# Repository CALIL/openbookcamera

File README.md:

# Open Book Camera v1

汎用的なデバイスで構成される高速な書影撮影システム

## コンセプト

- 書影（本の表示画像）キャプチャ用のスキャナデバイス
- 本を置いたら自動撮影
- 表紙・裏表紙・背の3面を高速撮影（2秒程度）
- ネットワーク接続なしでスタンドアロン動作

## システム構成

## Installation

Windows:

- [Anaconda](https://www.anaconda.com/download/) Python3.7 をインストール
- [libjpeg-turbo](https://libjpeg-turbo.org/Documentation/Documentation) をインストール [libjpeg-turbo-1.5.3-vc64.exe](https://sourceforge.net/projects/libjpeg-turbo/files/1.5.3/libjpeg-turbo-1.5.3-vc64.exe/download)
- [Visual C++ Redistributable Packages for Visual Studio 2013](https://www.microsoft.com/en-US/download/details.aspx?id=40784)をインストール（pyzbarが依存）

```sh
conda install opencv==3.4.2
pip install -r requirements.txt
python capture.py
```

## キーボード操作

| キー | 役割                     |
|------|--------------------------|
| 0    | コントローラーリセット   |
| 1    | 上面のカメラに切り替える |
| 2    | 下面のカメラに切り替える |
| 3    | 背面のカメラに切り替える |
| 4    | 距離センサのテスト       |
| c    | カメラの設定画面を開く   |
| ESC  | システム終了             |
| Enter| 手動撮影                 |

1→c 2→c と操作することで各カメラの設定を順次調整できます。調整結果は保存されません。

## 制御ボード

- Arudinoシールド互換サイズ
- MOSFETによる12V制御回路×4
- 各種センサ向けのコネクタ（2.5mmピッチ・XHシリーズ）
- [Pololu Arduino library for VL53L0X](https://github.com/pololu/vl53l0x-arduino)
- 光電センサ [Z2T-2000N](https://www.optex-fa.jp/products/photo_sensor/amp/z_eco/index.html) を本が置かれたことを検出するセンサとして採用

## UVCカメラ

- [UVC規格](https://en.wikipedia.org/wiki/USB_video_device_class)の汎用的なUSBカメラに対応
- カーリルでは[IPEVO社製V4K](https://www.ipevo.jp/v4k.html)を採用（800万画素）
- 各カメラを独立したUSBポートに接続すること（USBハブを用いた場合は帯域不足となる）

## 注意事項

- 輸送後にはフォーカス設定が変動する場合があります。最適な画質になる設定にソースコードを調整してください。
- 2019年12月購入以降のV4Kにおいて、色温度の設定が自動化できない不具合を確認しています。この問題は[openCV側の不具合](https://github.com/opencv/opencv/issues/13130)の可能性があります。cコマンドによるマニュアル設定をお願いします。
 
## Release History

* 0.0.1 Work in progress
* 1.0.0 正式リリース
* 1.1.0 V4K最新ファームウェアに対応
* 1.2.0 V4K最新ファームウェアに対応

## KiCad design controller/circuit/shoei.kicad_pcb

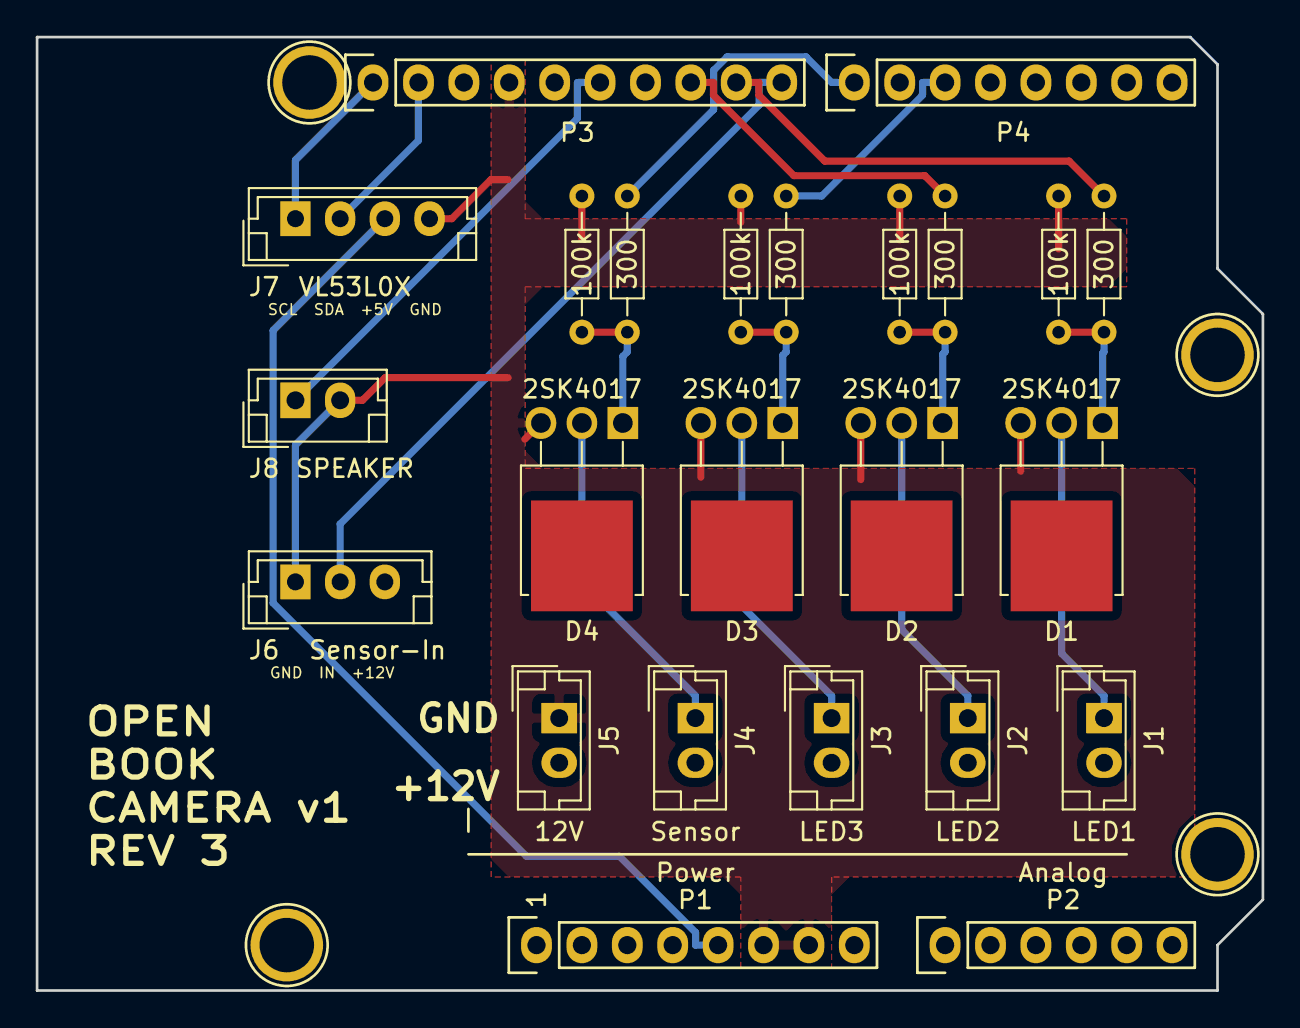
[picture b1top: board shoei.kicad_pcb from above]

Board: 2 copper layers, 68.6 x 53.3 mm, 28 parts (0 on the bottom side), 19 nets.

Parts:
D1, D2, D3, D4: 2SK4017; TO-251-3-1EP_Horizontal_TabDown
J1: LED1; JST_EH_B02B-EH-A_1x02_P2.50mm_Vertical
J2: LED2; JST_EH_B02B-EH-A_1x02_P2.50mm_Vertical
J3: LED3; JST_EH_B02B-EH-A_1x02_P2.50mm_Vertical
J4: Sensor; JST_EH_B02B-EH-A_1x02_P2.50mm_Vertical
J5: 12V; JST_EH_B02B-EH-A_1x02_P2.50mm_Vertical
J6: Sensor-In; JST_EH_B03B-EH-A_1x03_P2.50mm_Vertical
J7: VL53L0X; JST_EH_B04B-EH-A_1x04_P2.50mm_Vertical
J8: SPEAKER; JST_EH_B02B-EH-A_1x02_P2.50mm_Vertical
P1: Power; Socket_Strip_Arduino_1x08
P2: Analog; Socket_Strip_Arduino_1x06
P3: Digital; Socket_Strip_Arduino_1x10
P4: Digital; Socket_Strip_Arduino_1x08
P5, P6, P7, P8: CONN_01X01; Arduino_1pin
R1, R2, R3, R4: 300; R_Axial_DIN0204_L3.6mm_D1.6mm_P7.62mm_Horizontal
R5, R6, R7, R8: 100k; R_Axial_DIN0204_L3.6mm_D1.6mm_P7.62mm_Horizontal

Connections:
+5V: J7.3, P1.5
+12V: J1.2, J2.2, J3.2, J4.2, J5.2, J6.3, P1.8
/5(**): P4.3, R3.1
/7: P4.1, R4.1
/8: J6.2, P3.10
/9(**): P3.9, R1.1
/10(**/SS): P3.8, R2.1
/12(MISO): J8.1, P3.6
/A4(SDA): J7.2, P3.2
/A5(SCL): J7.1, P3.1
GND: D1.3, D2.3, D3.3, D4.3, J5.1, J6.1, J7.4, J8.2, P1.6, P1.7, P3.4, R5.2, R6.2, R7.2, R8.2
unnamed: D1.1, R1.2, R5.1
unnamed: D1.2, J1.1
unnamed: D2.1, R2.2, R6.1
unnamed: D2.2, J2.1
unnamed: D3.1, R3.2, R7.1
unnamed: D3.2, J3.1
unnamed: D4.1, R4.2, R8.1
unnamed: D4.2, J4.1

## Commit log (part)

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2018-08-17 add firmware/Controller.ino
2018-08-17 add circuit board (KiCad)
2018-08-17 add order data
2018-08-17 add 3d image
2018-08-17 add capture application
2018-08-18 use turbo-jpeg on save
2018-08-18 move capture.py
2018-08-18 add requirements.txt
2018-08-18 fix data-path
2018-08-18 document for installation
2018-08-18 add diagram.png
2018-08-18 add document
2018-08-18 add picture
2018-08-18 fix picture
2018-08-18 fix document
2018-08-18 update document
2018-08-18 add dependency to requirements.txt
2018-08-18 fix doc
2018-08-18 add doc
2018-08-18 change serial rate to 115200
2018-08-18 fix lunch check process
2018-08-25 update enclosure
2018-08-30 update pcb silk
2018-08-30 add datasheet
2018-10-01 add controller-attachment
2018-10-28 fix focus
2018-11-05 update install explain
2018-11-06 update parts
2018-11-06 update doc
2019-05-06 update（opencvの最新版でフォーカスが調整できなくなる問題に対応）
2019-05-06 図面を追加
2019-10-10 新しいV4Kファームウェアに対応 ビデオキャプチャでDirectShowを明確に指定
2019-10-10 ドキュメントを更新
2020-03-16 V4K最新ファームウェアに対応
2020-03-16 上下カメラの認識率を改善
2020-03-16 ドキュメントを追加
2020-04-02 add web
2020-04-02 add README.md
2021-04-12 Deploying to gh-pages from @ CALIL/openbookcamera@34eb7b73edf3827435af7b91a84dcf0a4dfec82f 🚀
2021-04-12 Initial gh-pages commit
2021-04-12 Deploying to gh-pages from @ CALIL/openbookcamera@eea38875df0d3015b29e373392499a17648cc81e 🚀
2022-03-26 Bump minimist from 1.2.5 to 1.2.6 in /web
    Bumps [minimist](https://github.com/substack/minimist) from 1.2.5 to 1.2.6.
    - [Release notes](https://github.com/substack/minimist/releases)
    - [Commits](https://github.com/substack/minimist/compare/1.2.5...1.2.6)
    ---
    updated-dependencies:
    - dependency-name: minimist
2022-05-16 Bump ws from 5.2.2 to 5.2.3 in /web
    Bumps [ws](https://github.com/websockets/ws) from 5.2.2 to 5.2.3.
    - [Release notes](https://github.com/websockets/ws/releases)
    - [Commits](https://github.com/websockets/ws/compare/5.2.2...5.2.3)
    ---
    updated-dependencies:
    - dependency-name: ws
2023-03-04 Bump minimist from 1.2.5 to 1.2.8 in /web
    Bumps [minimist](https://github.com/minimistjs/minimist) from 1.2.5 to 1.2.8.
    - [Release notes](https://github.com/minimistjs/minimist/releases)
    - [Changelog](https://github.com/minimistjs/minimist/blob/main/CHANGELOG.md)
    - [Commits](https://github.com/minimistjs/minimist/compare/v1.2.5...v1.2.8)
    ---
    updated-dependencies:
2023-04-29 Bump json5 from 1.0.1 to 1.0.2 in /web
    Bumps [json5](https://github.com/json5/json5) from 1.0.1 to 1.0.2.
    - [Release notes](https://github.com/json5/json5/releases)
    - [Changelog](https://github.com/json5/json5/blob/main/CHANGELOG.md)
    - [Commits](https://github.com/json5/json5/compare/v1.0.1...v1.0.2)
    ---
    updated-dependencies:
2023-04-29 Bump decode-uri-component from 0.2.0 to 0.2.2 in /web
    Bumps [decode-uri-component](https://github.com/SamVerschueren/decode-uri-component) from 0.2.0 to 0.2.2.
    - [Release notes](https://github.com/SamVerschueren/decode-uri-component/releases)
    - [Commits](https://github.com/SamVerschueren/decode-uri-component/compare/v0.2.0...v0.2.2)
    ---
    updated-dependencies:
    - dependency-name: decode-uri-component
2023-04-29 Bump ansi-regex from 3.0.0 to 3.0.1 in /web
    Bumps [ansi-regex](https://github.com/chalk/ansi-regex) from 3.0.0 to 3.0.1.
    - [Release notes](https://github.com/chalk/ansi-regex/releases)
    - [Commits](https://github.com/chalk/ansi-regex/compare/v3.0.0...v3.0.1)
    ---
    updated-dependencies:
    - dependency-name: ansi-regex
2023-04-29 Bump minimatch from 3.0.4 to 3.1.2 in /web
    Bumps [minimatch](https://github.com/isaacs/minimatch) from 3.0.4 to 3.1.2.
    - [Release notes](https://github.com/isaacs/minimatch/releases)
    - [Changelog](https://github.com/isaacs/minimatch/blob/main/changelog.md)
    - [Commits](https://github.com/isaacs/minimatch/compare/v3.0.4...v3.1.2)
    ---
    updated-dependencies:
2023-04-29 Bump qs from 6.5.2 to 6.5.3 in /web
    Bumps [qs](https://github.com/ljharb/qs) from 6.5.2 to 6.5.3.
    - [Release notes](https://github.com/ljharb/qs/releases)
    - [Changelog](https://github.com/ljharb/qs/blob/main/CHANGELOG.md)
    - [Commits](https://github.com/ljharb/qs/compare/v6.5.2...v6.5.3)
    ---
    updated-dependencies:
2026-03-12 fix(web): cssnanoのバージョンを4.1.10から7.1.3に更新
    - web/package.jsonのdevDependencies内でcssnanoのバージョンを4.1.10から7.1.3に変更しました。
2026-03-12 fix(web): cssnanoのバージョンを4.1.10に戻す
    devDependenciesのcssnanoのバージョンを4.1.10に変更しました。
2026-03-12 feat: package.jsonの更新
    - "main"フィールドを削除しました。
    - "build"スクリプトのオプションを変更し、"--out-dir"を"--dist-dir"に修正しました。
    - "devDependencies"を更新し、"cssnano"と"parcel-bundler"を削除し、"@parcel/transformer-sass"と"parcel"を追加しました。
2026-03-12 fix: GitHub Actionsのcheckoutとデプロイアクションのバージョンを更新
    - actions/checkoutをv2.3.1からv4に更新
    - JamesIves/github-pages-deploy-actionを4.1.1からv4に更新
2026-03-12 Deploying to gh-pages from @ CALIL/openbookcamera@4b5c78a269f5f62fb480fd0e64a4ce4f44bfb191 🚀
2026-03-26 Bump picomatch from 4.0.3 to 4.0.4 in /web
    Bumps [picomatch](https://github.com/micromatch/picomatch) from 4.0.3 to 4.0.4.
    - [Release notes](https://github.com/micromatch/picomatch/releases)
    - [Changelog](https://github.com/micromatch/picomatch/blob/master/CHANGELOG.md)
    - [Commits](https://github.com/micromatch/picomatch/compare/4.0.3...4.0.4)
    ---
    updated-dependencies:
2026-05-13 ci: npm install/ciに--ignore-scriptsを追加
2026-05-21 chore: add Dependabot cooldown configuration
2026-05-21 chore: npm install → npm ci --ignore-scripts in .github/workflows/gh-pages.yml
2026-05-21 Bump sass from 1.98.0 to 1.99.0 in /web
    Bumps [sass](https://github.com/sass/dart-sass) from 1.98.0 to 1.99.0.
    - [Release notes](https://github.com/sass/dart-sass/releases)
    - [Changelog](https://github.com/sass/dart-sass/blob/main/CHANGELOG.md)
    - [Commits](https://github.com/sass/dart-sass/compare/1.98.0...1.99.0)
    ---
    updated-dependencies:
2026-05-21 fix: Dependabotバージョンアップデートを無効化（セキュリティのみ有効）
